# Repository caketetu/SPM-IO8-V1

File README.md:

# SPM-IO8-V1
Simple Programable Module 絶縁8入力8出力モジュール

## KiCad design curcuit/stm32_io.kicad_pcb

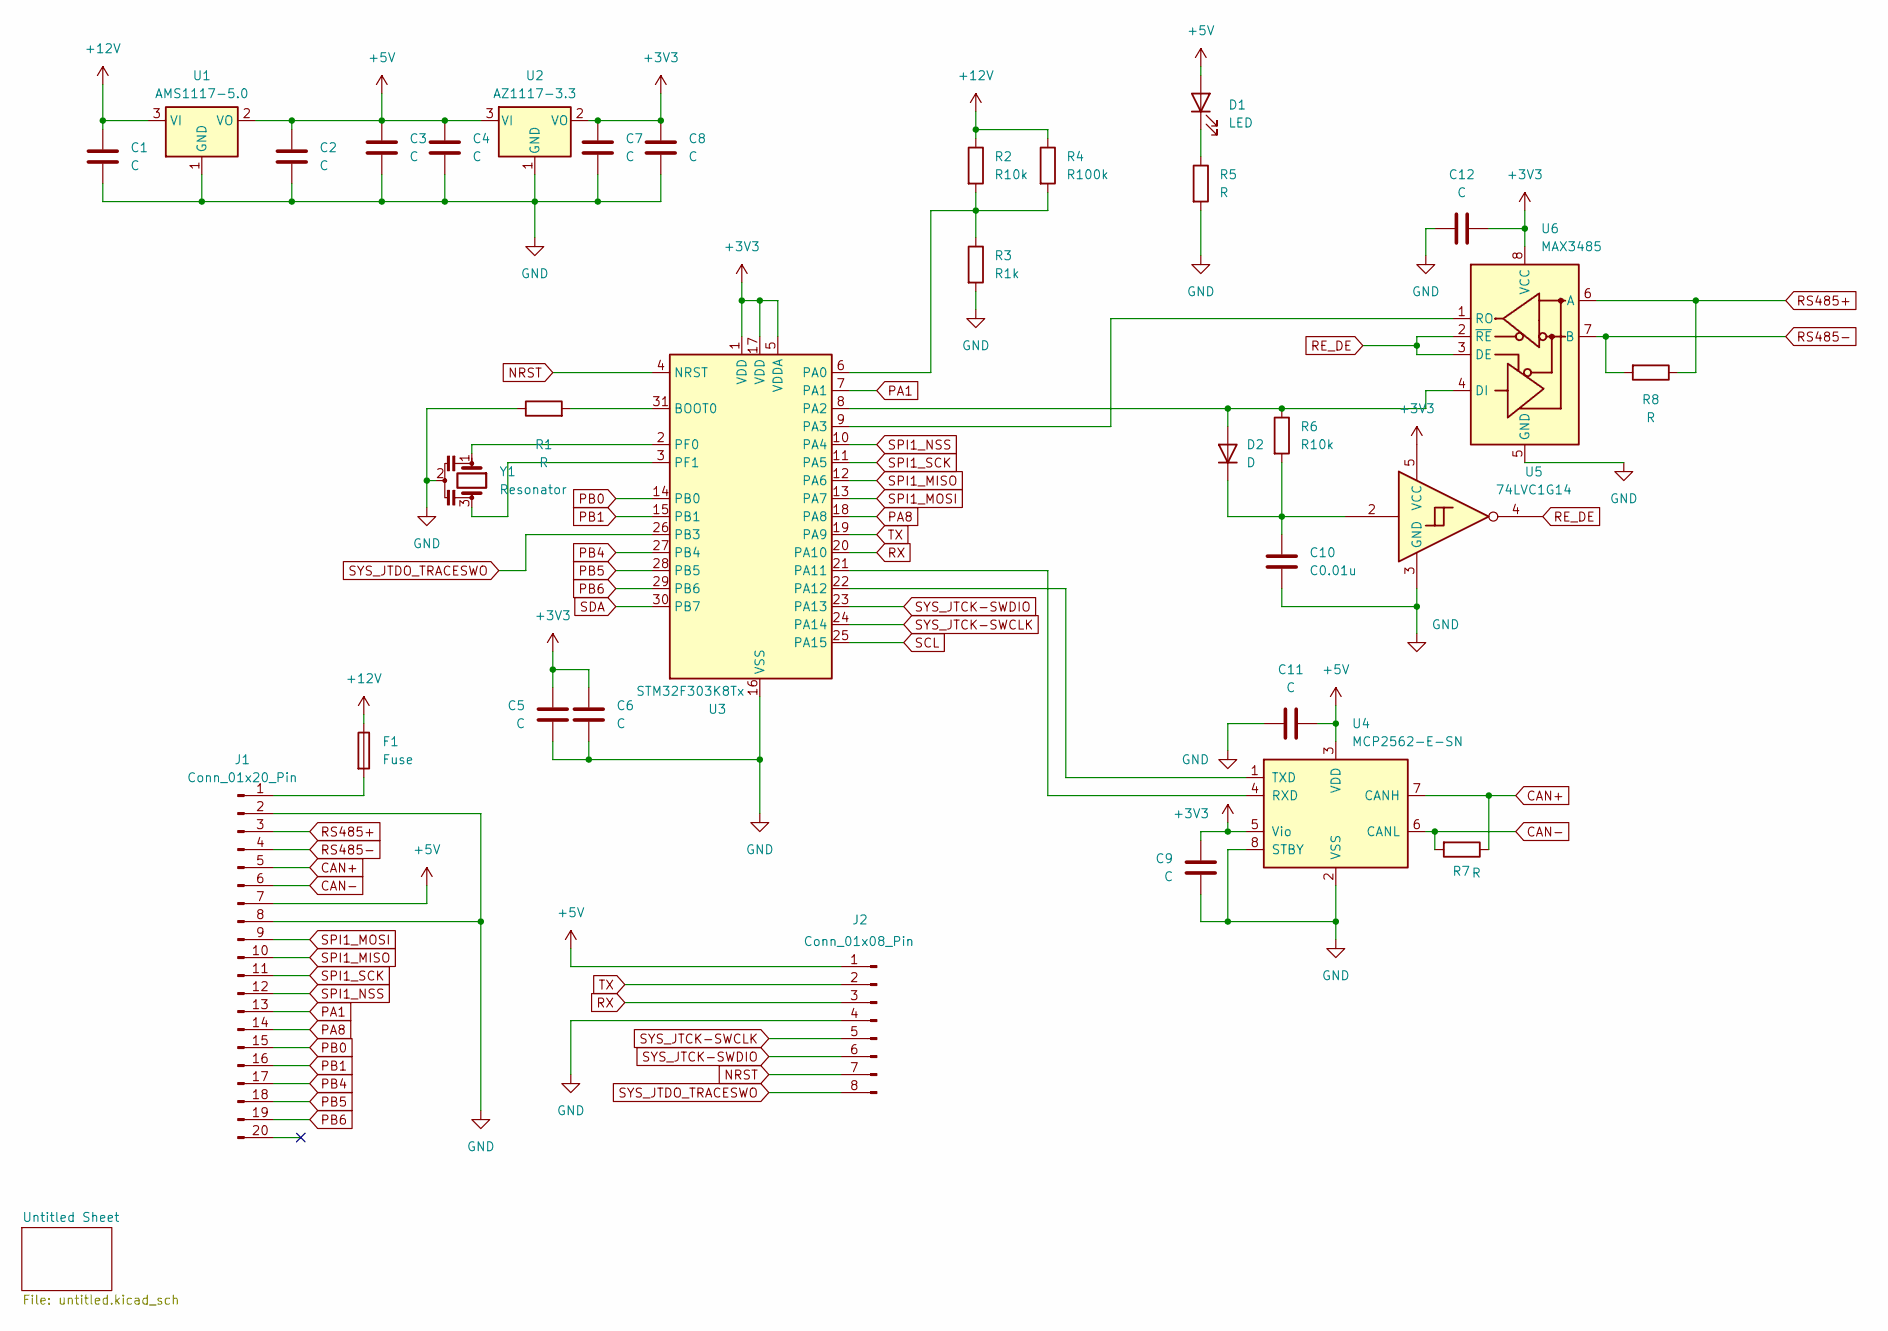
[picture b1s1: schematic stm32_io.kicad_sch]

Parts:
C1, C2, C4: C; C_0805_2012Metric
C3, C5, C6, C7, C8, C9, C11, C12: C; C_0603_1608Metric
C10: C0.01u; C_0805_2012Metric
D1: LED; LED_1206_3216Metric
D2: D; D_1206_3216Metric
F1: Fuse; Fuse_1206_3216Metric
J1: Conn_01x20_Pin; PinHeader_1x20_P2.54mm_Vertical
J2: Conn_01x08_Pin; JST_ZH_B8B-ZR_1x08_P1.50mm_Vertical
R1, R5: R; R_0603_1608Metric
R2, R6: R10k; R_0603_1608Metric
R3: R1k; R_0603_1608Metric
R4: R100k; R_0603_1608Metric
R7, R8: R; R_1206_3216Metric
U1: AMS1117-5.0; SOT-223-3_TabPin2
U2: AZ1117-3.3; SOT-223-3_TabPin2
U3: STM32F303K8Tx; LQFP-32_7x7mm_P0.8mm
U4: MCP2562-E-SN; SOIC-8_3.9x4.9mm_P1.27mm
U5: 74LVC1G14; SOT-23-5
U6: MAX3485; SOIC-8_3.9x4.9mm_P1.27mm
Y1: Resonator; Resonator_SMD_Murata_CSTxExxV-3Pin_3.0x1.1mm_HandSoldering

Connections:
+3V3: C5.1, C6.1, C7.1, C8.1, C9.1, C12.2, U2.2 (VO), U3.1 (VDD), U3.5 (VDDA), U3.17 (VDD), U4.5 (Vio), U5.5 (VCC), U6.8 (VCC)
+5V: C2.1, C3.1, C4.1, C11.2, D1.2 (A), J1.7, J2.1, U1.2 (VO), U2.3 (VI), U4.3 (VDD); also elsewhere on the board
+12V: C1.1, F1.1, R2.1, R4.1, U1.3 (VI)
CAN+: J1.5, R7.1, U4.7 (CANH)
CAN-: J1.6, R7.2, U4.6 (CANL)
GND: C1.2, C2.2, C3.2, C4.2, C5.2, C6.2, C7.2, C8.2, C9.2, C10.2, C11.1, C12.1, J1.2, J1.8, J2.4, R1.1, R3.2, R5.2, U1.1 (GND), U2.1 (GND), U3.16 (VSS), U3.32 (VSS), U4.2 (VSS), U4.8 (STBY), U5.3 (GND), U6.5 (GND), Y1.2; also elsewhere on the board
NRST: J2.7, U3.4 (NRST)
unnamed: D1.1 (K), R5.1
unnamed: D2.2 (A), R6.1, U3.8 (PA2), U6.4 (DI)
unnamed: C10.1, D2.1 (K), R6.2, U5.2
unnamed: F1.2, J1.1
unnamed: R1.2, U3.31 (BOOT0)
unnamed: R2.2, R3.1, R4.2, U3.6 (PA0)
unnamed: U3.9 (PA3), U6.1 (RO)
unnamed: U3.21 (PA11), U4.4 (RXD)
unnamed: U3.22 (PA12), U4.1 (TXD)
unnamed: U3.2 (PF0), Y1.1
unnamed: U3.3 (PF1), Y1.3
PA1: J1.13, U3.7 (PA1)
PA8: J1.14, U3.18 (PA8)
PB0: J1.15, U3.14 (PB0)
PB1: J1.16, U3.15 (PB1)
PB4: J1.17, U3.27 (PB4)
PB5: J1.18, U3.28 (PB5)
PB6: J1.19, U3.29 (PB6)
RE_DE: U5.4, U6.2 (~RE), U6.3 (DE)
RS485+: J1.3, R8.1, U6.6 (A)
RS485-: J1.4, R8.2, U6.7 (B)
RX: J2.3, U3.20 (PA10)
SCL: U3.25 (PA15); also elsewhere on the board
SDA: U3.30 (PB7); also elsewhere on the board
SPI1_MISO: J1.10, U3.12 (PA6)
SPI1_MOSI: J1.9, U3.13 (PA7)
SPI1_NSS: J1.12, U3.10 (PA4)
SPI1_SCK: J1.11, U3.11 (PA5)
SYS_JTCK-SWCLK: J2.5, U3.24 (PA14)
SYS_JTCK-SWDIO: J2.6, U3.23 (PA13)
SYS_JTDO_TRACESWO: J2.8, U3.26 (PB3)
TX: J2.2, U3.19 (PA9)

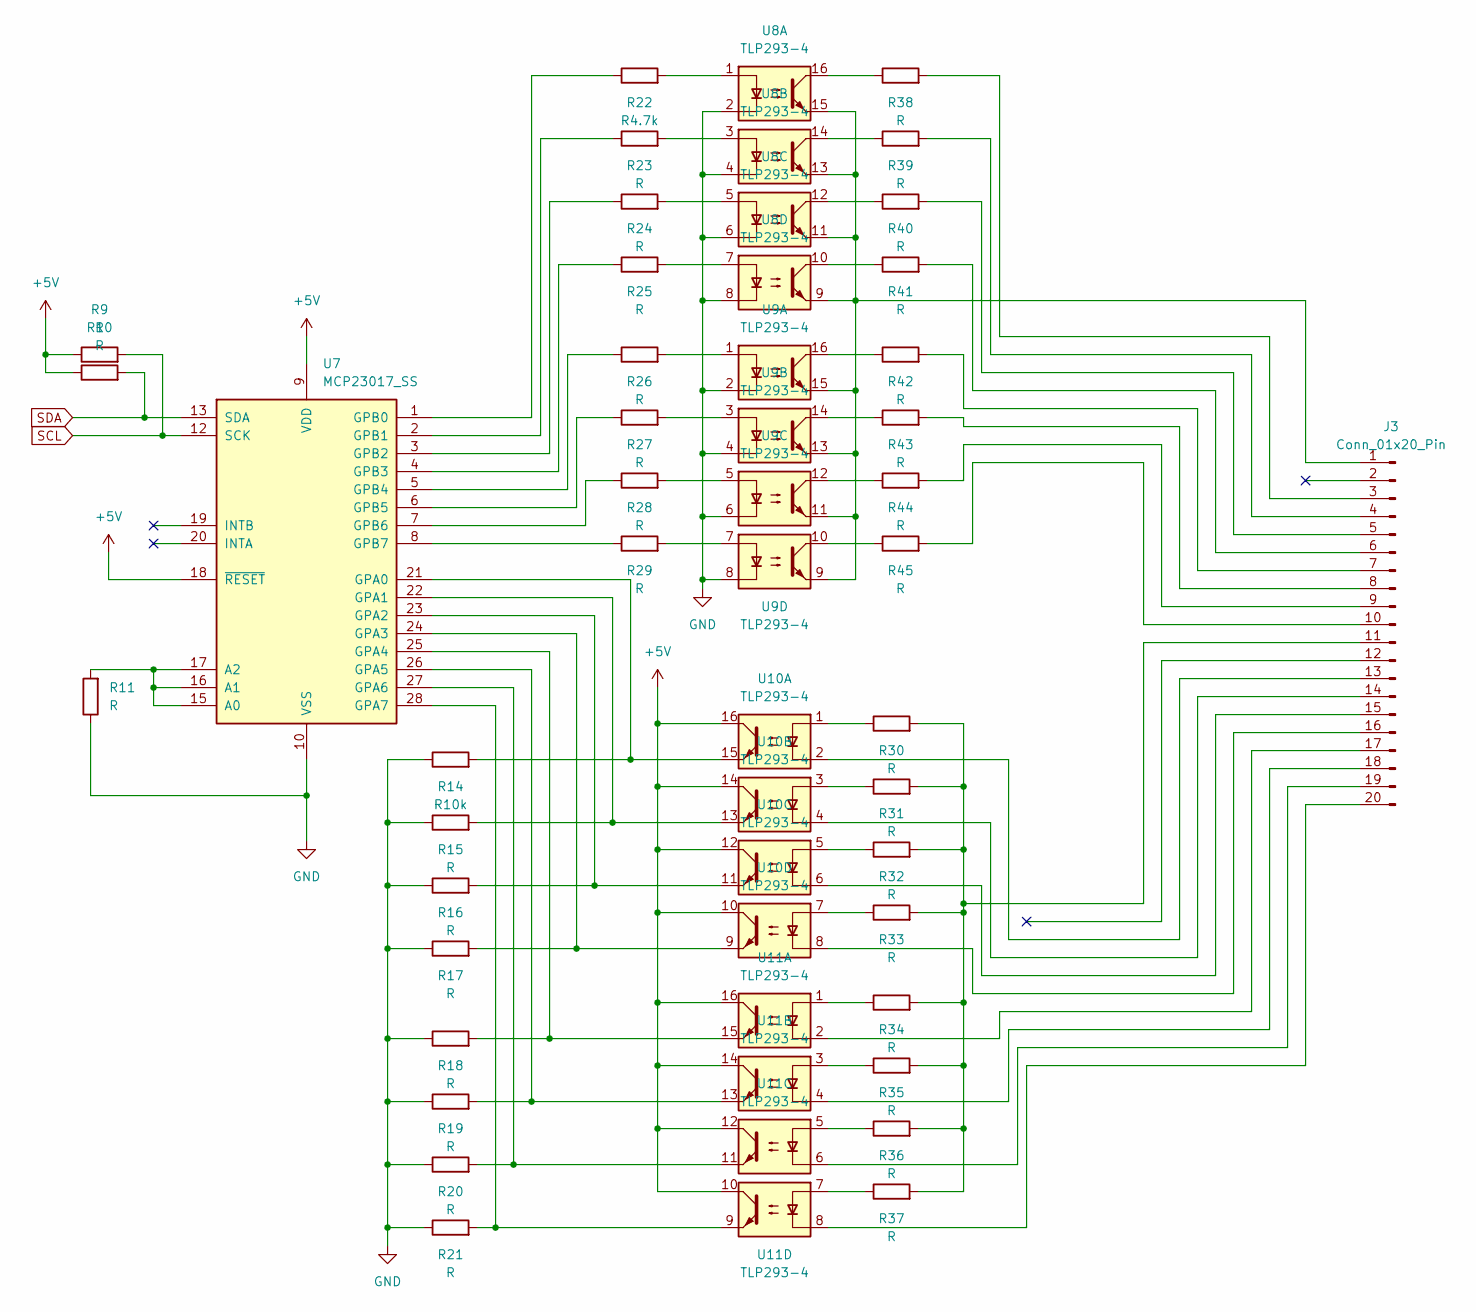
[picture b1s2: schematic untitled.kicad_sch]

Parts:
J3: Conn_01x20_Pin; PinHeader_1x20_P2.54mm_Vertical
R9, R10, R11, R15, R16, R17, R18, R19, R20, R21, R23, R24, R25, R26, R27, R28, R29, R30, R31, R32, R33, R34, R35, R36, R37, R38, R39, R40, R41, R42, R43, R44, R45: R; R_0603_1608Metric
R14: R10k; R_0603_1608Metric
R22: R4.7k; R_0603_1608Metric
U7: MCP23017_SS; SSOP-28_5.3x10.2mm_P0.65mm
U8, U9, U10, U11: TLP293-4; SOIC-16_4.55x10.3mm_P1.27mm

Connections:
+5V: R9.1, R10.1, U7.9 (VDD), U7.18 (~RESET), U10.10, U10.12, U10.14, U10.16, U11.10, U11.12, U11.14, U11.16; also elsewhere on the board
GND: R11.1, R14.1, R15.1, R16.1, R17.1, R18.1, R19.1, R20.1, R21.1, U7.10 (VSS), U8.2, U8.4, U8.6, U8.8, U9.2, U9.4, U9.6, U9.8; also elsewhere on the board
unnamed: J3.1, U8.9, U8.11, U8.13, U8.15, U9.9, U9.11, U9.13, U9.15
unnamed: J3.3, R38.2
unnamed: J3.4, R39.2
unnamed: J3.5, R40.2
unnamed: J3.6, R41.2
unnamed: J3.7, R42.2
unnamed: J3.8, R43.2
unnamed: J3.9, R44.2
unnamed: J3.10, R45.2
unnamed: J3.11, R30.2, R31.2, R32.2, R33.2, R34.2, R35.2, R36.2, R37.2
unnamed: J3.13, U10.2
unnamed: J3.14, U10.4
unnamed: J3.15, U10.6
unnamed: J3.16, U10.8
unnamed: J3.17, U11.2
unnamed: J3.18, U11.4
unnamed: J3.19, U11.6
unnamed: J3.20, U11.8
unnamed: R22.2, U8.1
unnamed: R23.2, U8.3
unnamed: R24.2, U8.5
unnamed: R25.2, U8.7
unnamed: R26.2, U9.1
unnamed: R27.2, U9.3
unnamed: R28.2, U9.5
unnamed: R29.2, U9.7
unnamed: R30.1, U10.1
unnamed: R31.1, U10.3
unnamed: R32.1, U10.5
unnamed: R33.1, U10.7
unnamed: R34.1, U11.1
unnamed: R35.1, U11.3
unnamed: R36.1, U11.5
unnamed: R37.1, U11.7
unnamed: R38.1, U8.16
unnamed: R39.1, U8.14
unnamed: R40.1, U8.12
unnamed: R41.1, U8.10
unnamed: R42.1, U9.16
unnamed: R43.1, U9.14
unnamed: R44.1, U9.12
unnamed: R45.1, U9.10
unnamed: R11.2, U7.15 (A0), U7.16 (A1), U7.17 (A2)
unnamed: R14.2, U7.21 (GPA0), U10.15
unnamed: R15.2, U7.22 (GPA1), U10.13
unnamed: R16.2, U7.23 (GPA2), U10.11
unnamed: R17.2, U7.24 (GPA3), U10.9
unnamed: R18.2, U7.25 (GPA4), U11.15
unnamed: R19.2, U7.26 (GPA5), U11.13
unnamed: R20.2, U7.27 (GPA6), U11.11
unnamed: R21.2, U7.28 (GPA7), U11.9
unnamed: R22.1, U7.1 (GPB0)
unnamed: R23.1, U7.2 (GPB1)
unnamed: R24.1, U7.3 (GPB2)
unnamed: R25.1, U7.4 (GPB3)
unnamed: R26.1, U7.5 (GPB4)
unnamed: R27.1, U7.6 (GPB5)
unnamed: R28.1, U7.7 (GPB6)
unnamed: R29.1, U7.8 (GPB7)
SCL: R9.2, U7.12 (SCK); also elsewhere on the board
SDA: R10.2, U7.13 (SDA); also elsewhere on the board

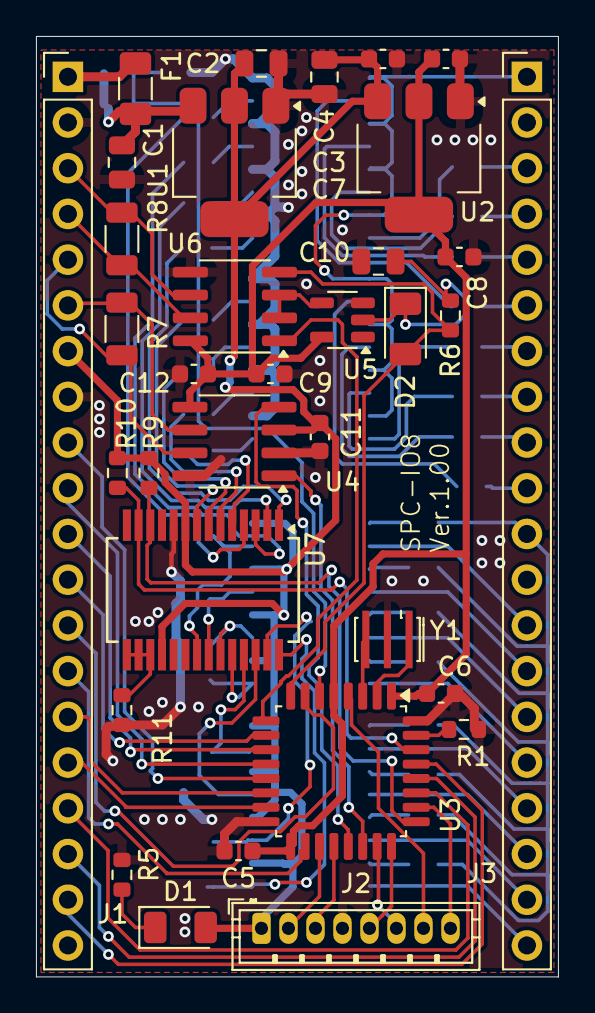
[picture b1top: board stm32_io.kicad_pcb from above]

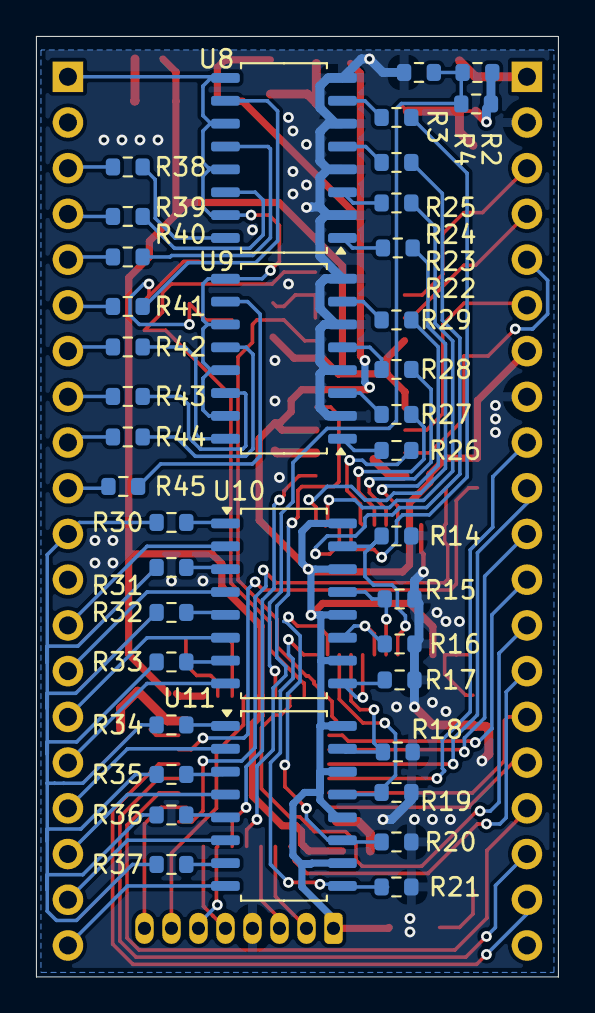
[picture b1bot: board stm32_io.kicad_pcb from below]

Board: 2 copper layers, 29.0 x 52.2 mm, 73 parts (39 on the bottom side), 98 nets.
